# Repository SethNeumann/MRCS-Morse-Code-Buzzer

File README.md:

# MRCS-Morse-Code-Buzzer
## License: Creative Commons Attribution-NonCommercial-ShareAlike

On many operations-oriented model railroads, particularly those
which a time-table and train-order (TT&TO) or tower-based dispatching
system, there is a need to provide telephone communications between
the dispatcher and the agent/operators. However, even on fairly
large model railroads with multiple agent/operators, the physical
distances between the operator positions are often insufficient to
allow the operators to reliably distinguish that “hey that’s my
phone ringing.”

The Morse Code Buzzer Controller board controls up to seven stations,
tapping out each ringing station's Telegraph code in Railroad Morse.
An additional output can be designated an “ambience” buzzer that
will randomly play one of several canned messages. These could be
train orders, news reports, or “inside jokes”

The board accepts a push button input, stops when the phone goes
off-hook (phone must have a suitable contact to provide an isolated
ground) and will drive loads of up to 0.5 Amp at up to 48 Volts DC.
All buzzer/sounder devices must use the same supply.  Sounders must
have have a coil resistance of greater than 40 ohms if using a 12V
supply.

Requires a 6-9 VDC power supply rated at at least 0.5A. not included.

The on-board Arduino Pro-Mini runs the
["station buzzers" sketch](https://github.com/stevew1154/station_buzzers)
by Steve Williams.

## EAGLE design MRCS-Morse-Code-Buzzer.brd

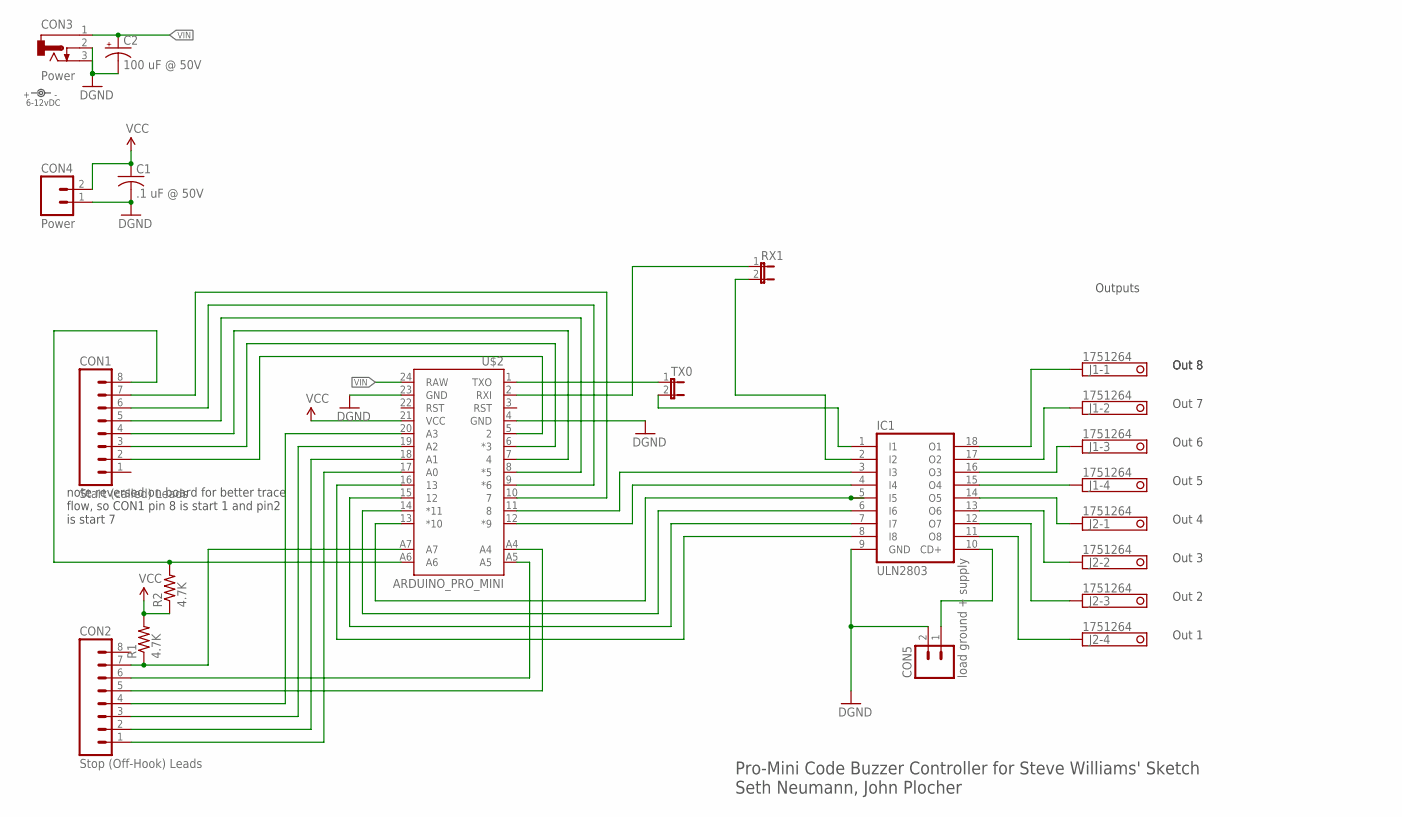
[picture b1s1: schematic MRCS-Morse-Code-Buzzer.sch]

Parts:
C1: .1 uF @ 50V; C025-030X050
C2: 100 uF @ 50V; E3.5-10
CON1: Start (called) Leads; 1X08_LOCK
CON2: Stop (Off-Hook) Leads; 1X08_LOCK
CON3: Power; DCJ0202
CON4: Power; MSTB2
CON5: load ground + supply; MSTB2
IC1: ULN2803; DIL18
J1, J2: 1751264
R1, R2: 4.7K; AXIAL-0.4-RES
RX1: JUMPER-2PTH; 1X02
TX0: JUMPER-2PTH; 1X02
U$2: ARDUINO_PRO_MINI
U$4: 6-12vDC; PWR_LABEL

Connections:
GND: C1.2, C2.-, CON3.2, CON3.3, CON4.1 (A), CON5.2 (B), IC1.9 (GND), U$2.4 (GND), U$2.23 (GND)
unnamed: IC1.18 (O1), J1.1
unnamed: IC1.17 (O2), J1.2
unnamed: IC1.16 (O3), J1.3
unnamed: IC1.15 (O4), J1.4
unnamed: IC1.14 (O5), J2.1
unnamed: IC1.13 (O6), J2.2
unnamed: IC1.12 (O7), J2.3
unnamed: IC1.11 (O8), J2.4
unnamed: CON1.2, U$2.5 (2)
unnamed: CON1.3, U$2.6 (*3)
unnamed: CON1.4, U$2.7 (4)
unnamed: CON1.5, U$2.8 (*5)
unnamed: CON1.6, U$2.9 (*6)
unnamed: CON1.7, U$2.10 (7)
unnamed: CON1.8, R2.P$2 (2), U$2.A6
unnamed: CON2.7, R1.P$1 (1), U$2.A7
unnamed: CON2.1, U$2.17 (A0)
unnamed: IC1.3 (I3), U$2.11 (8)
unnamed: IC1.4 (I4), U$2.12 (*9)
unnamed: IC1.8 (I8), U$2.16 (13)
unnamed: IC1.5 (I5), U$2.13 (*10)
unnamed: IC1.6 (I6), U$2.14 (*11)
unnamed: IC1.7 (I7), U$2.15 (12)
unnamed: CON2.2, U$2.18 (A1)
unnamed: CON2.3, U$2.19 (A2)
unnamed: CON2.4, U$2.20 (A3)
unnamed: CON2.5, U$2.A4
unnamed: CON2.6, U$2.A5
unnamed: TX0.1, U$2.1 (TXO)
unnamed: IC1.1 (I1), TX0.2
unnamed: IC1.2 (I2), RX1.2
unnamed: CON5.1 (A), IC1.10 (CD+)
unnamed: RX1.1, U$2.2 (RXI)
VCC: C1.1, CON4.2 (B), R1.P$2 (2), R2.P$1 (1), U$2.21 (VCC)
VIN: C2.+, CON3.1, U$2.24 (RAW)

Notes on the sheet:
Pro-Mini Code Buzzer Controller for Steve Williams' Sketch Seth Neumann, John Plocher
Outputs
Out 8
Out 7
Out 6
Out 5
Out 4
Out 3
Out 2
Out 1
note reversed on board for better trace flow, so CON1 pin 8 is start 1 and pin2 is start 7

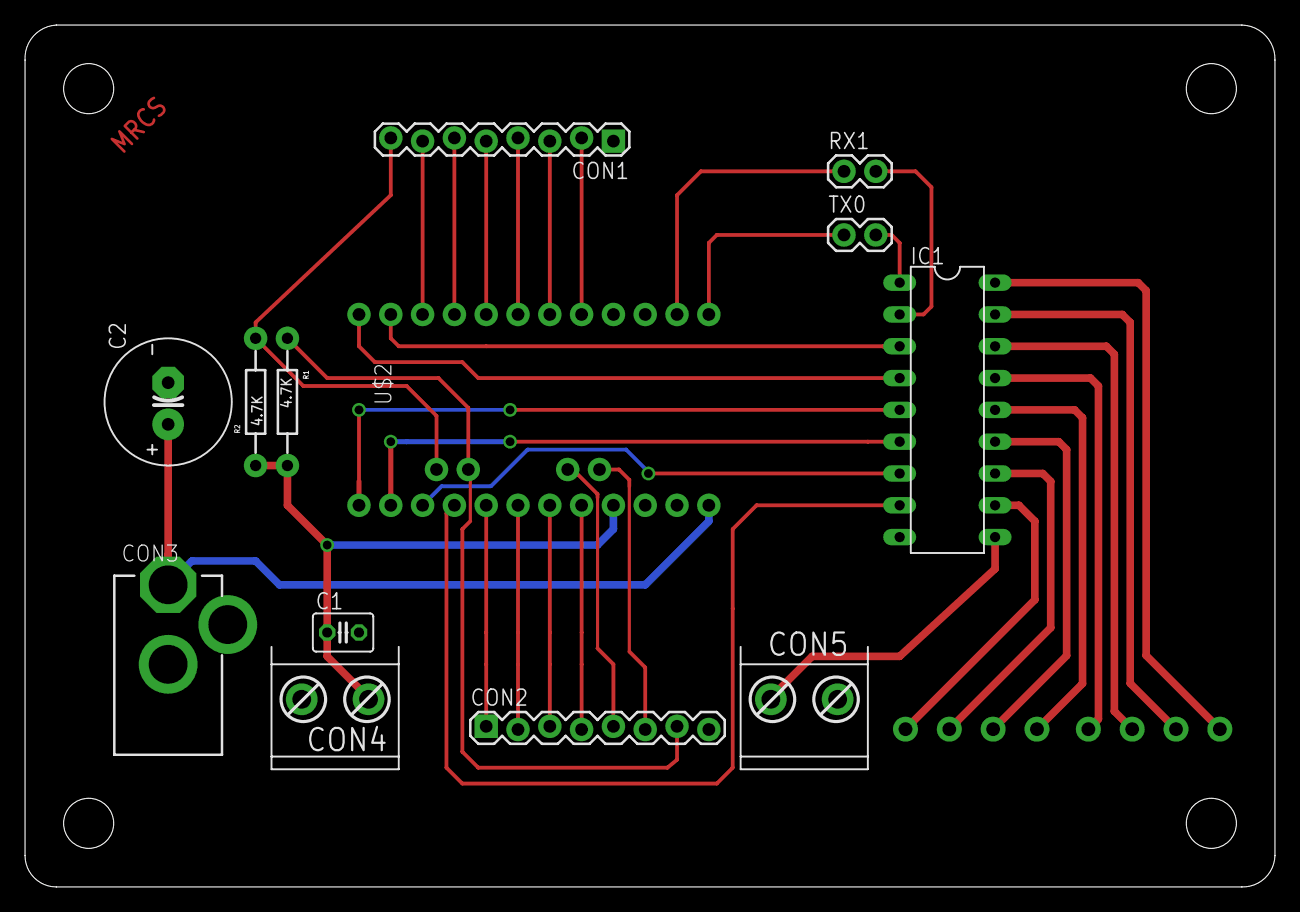
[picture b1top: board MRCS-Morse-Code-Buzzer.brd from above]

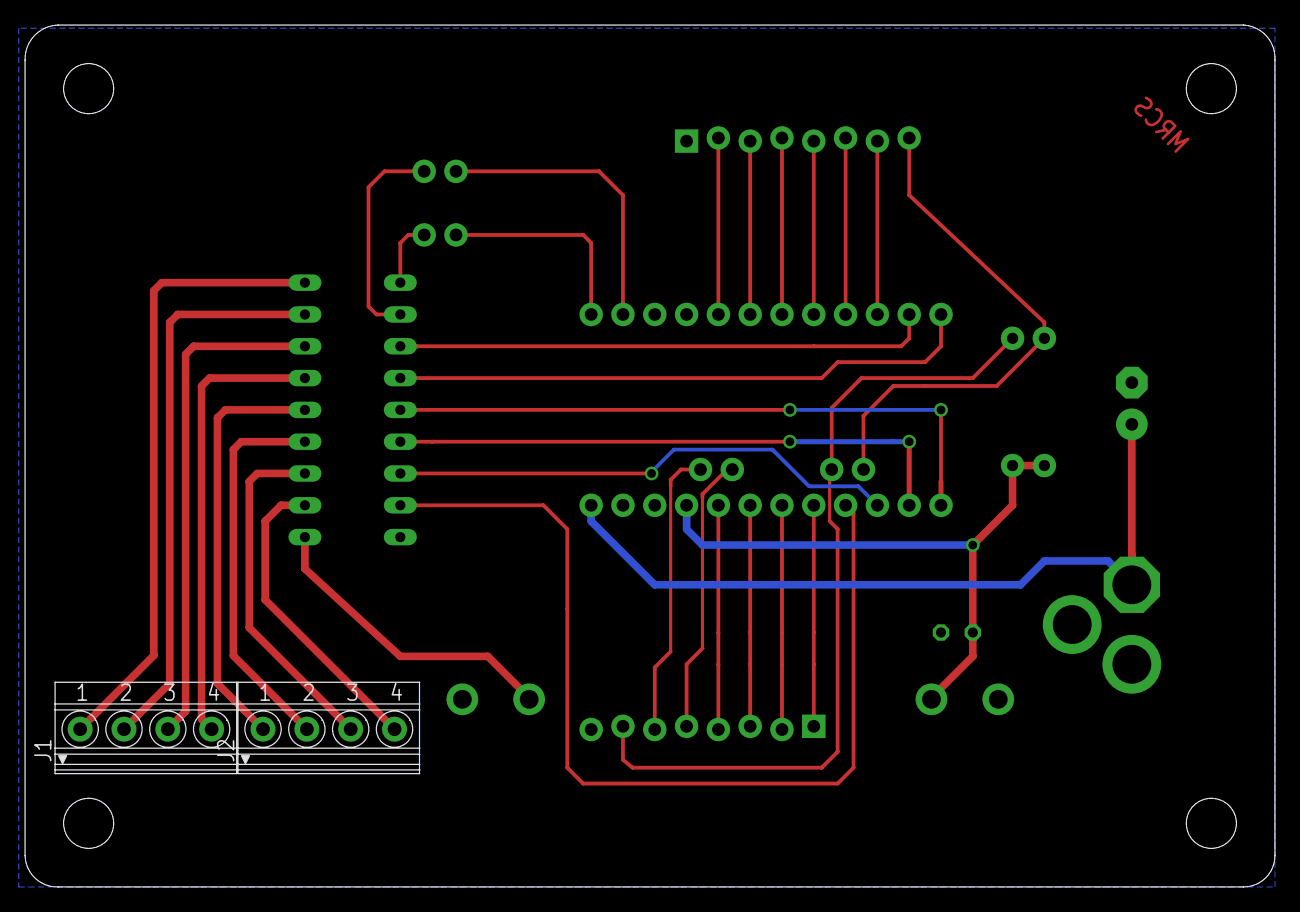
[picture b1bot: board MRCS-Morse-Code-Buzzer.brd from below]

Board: 2 copper layers, 99.8 x 68.8 mm, 18 parts (2 on the bottom side), 36 nets.

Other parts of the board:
U$1: BOARD-DINRAIL-2.71IN-MRCS
U$3: CA-PROP65-BACK

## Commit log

2019-11-28 ensured License is CC-NC-SA
2019-11-28 Telephone Tag
2019-12-02 test of git

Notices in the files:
parts and their libraries:
SparkFun-Boards-modified: Licensing: Creative Commons ShareAlike 4.0 International - https://creativecommons.org/licenses/by-sa/4.0
